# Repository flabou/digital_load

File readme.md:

# Digital load
This is a digital load circuit, project is WIP.
Intended features are:
- USB type-C connector with USB-2.0 supply (5V 500mA)
- Oled display to show current setting (and maybe other stuff)
- Encoder wheel with push-button to change current value
- Ability to connect several circuit (only one with screen, encoder, and usb supply) which will communicate through I2C and share the load (to reach higher current load)
- Several sense resistors to increase dynamic range.
- Maximum current and voltage are to be determined, current will probably be on the order of 1 to 5 amps max, ~1uA min
- USB serial interface, maybe to control from computer and read measured current points, this would allow to specify curve for the load for instance, if there's a use for it.

# Screenshots

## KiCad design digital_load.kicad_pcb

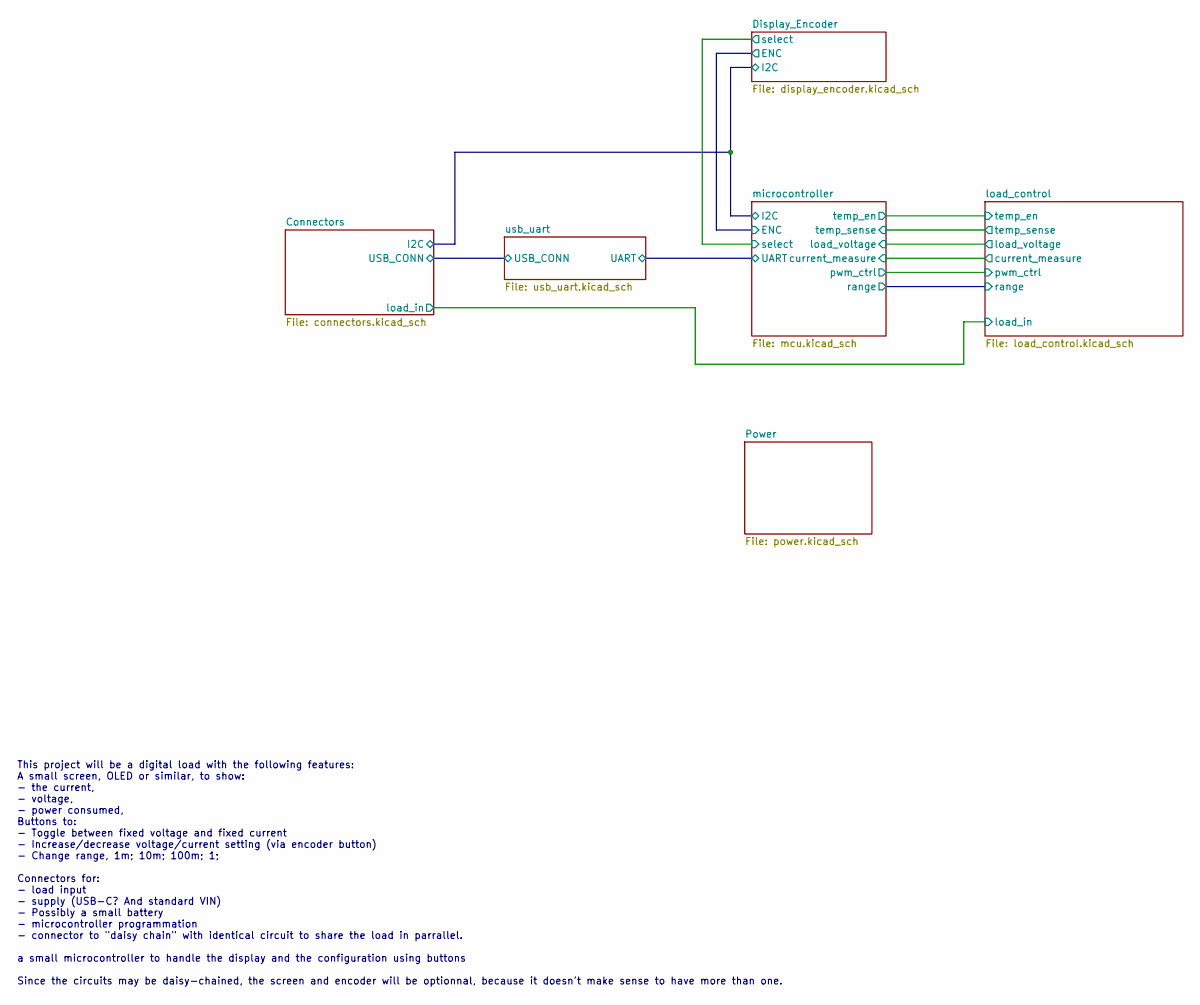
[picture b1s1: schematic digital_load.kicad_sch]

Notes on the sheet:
This project will be a digital load with the following features: A small screen, OLED or similar, to show: - the current, - voltage, - power consumed, Buttons to: - Toggle between fixed voltage and fixed current - Increase/decrease voltage/current setting (via encoder button) - Change range, 1m; 10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

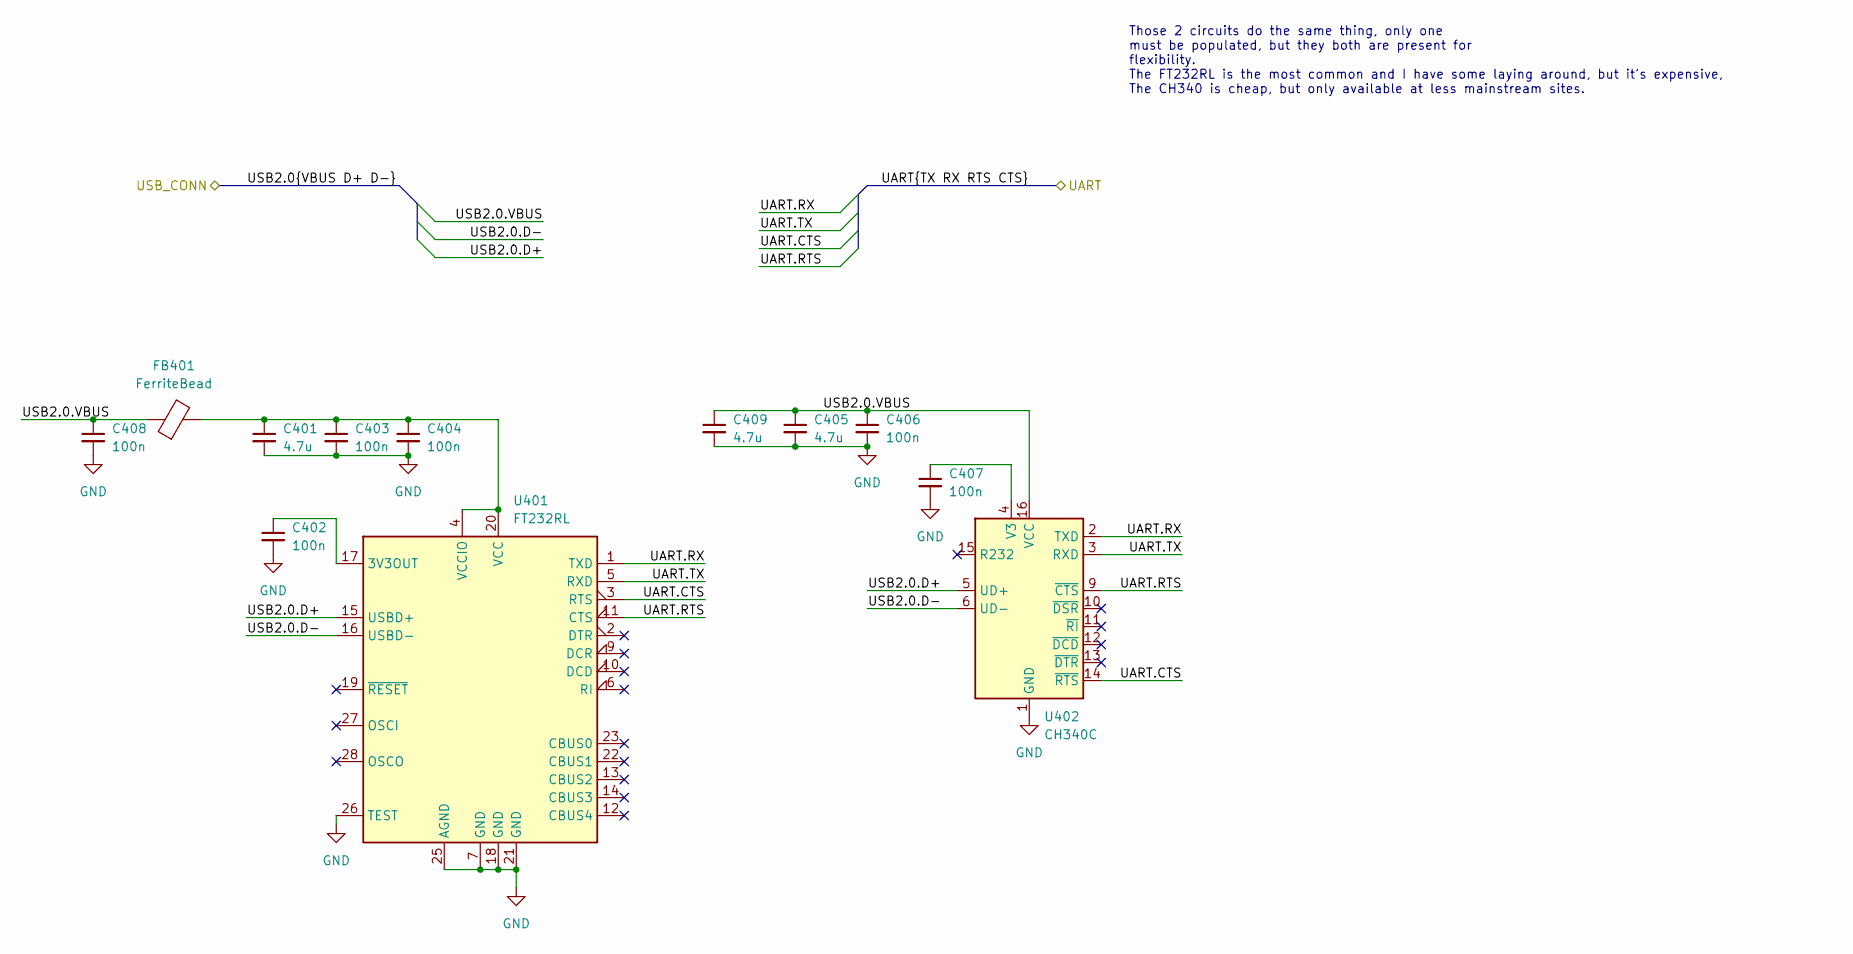
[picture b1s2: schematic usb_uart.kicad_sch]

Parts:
C401, C405, C409: 4.7u; C_0805_2012Metric; PartNumber Generic
C402, C403, C404, C406, C407, C408: 100n; C_0402_1005Metric; PartNumber Generic
FB401: FerriteBead; L_0805_2012Metric; PartNumber MH2029-400Y
U401: FT232RL; SSOP-28_5.3x10.2mm_P0.65mm; PartNumber FT232RL
U402: CH340C; SOIC-16_3.9x9.9mm_P1.27mm; PartNumber CH340C

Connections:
+5V: C405.1, C406.1, C408.1, C409.1, FB401.1, U402.16 (VCC); also elsewhere on the board
/Connectors/USB2.0.D+: U401.15 (USBD+), U402.5 (UD+); also elsewhere on the board
/Connectors/USB2.0.D-: U401.16 (USBD-), U402.6 (UD-); also elsewhere on the board
/microcontroller/UART.CTS: U401.3 (RTS), U402.14 (~RTS); also elsewhere on the board
/microcontroller/UART.RTS: U401.11 (CTS), U402.9 (~CTS); also elsewhere on the board
/microcontroller/UART.RX: U401.1 (TXD), U402.2 (TXD); also elsewhere on the board
/microcontroller/UART.TX: U401.5 (RXD), U402.3 (RXD); also elsewhere on the board
GND: C401.2, C402.2, C403.2, C404.2, C405.2, C406.2, C407.2, C408.2, C409.2, U401.7 (GND), U401.18 (GND), U401.21 (GND), U401.25 (AGND), U401.26 (TEST), U402.1 (GND); also elsewhere on the board
unnamed: C401.1, C403.1, C404.1, FB401.2, U401.4 (VCCIO), U401.20 (VCC)
unnamed: C402.1, U401.17 (3V3OUT)
unnamed: C407.1, U402.4 (V3)

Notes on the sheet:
Those 2 circuits do the same thing, only one must be populated, but they both are present for flexibility. The FT232RL is the most common and I have some laying around, but it's expensive, The CH340 is cheap, but only available at less mainstream sites.

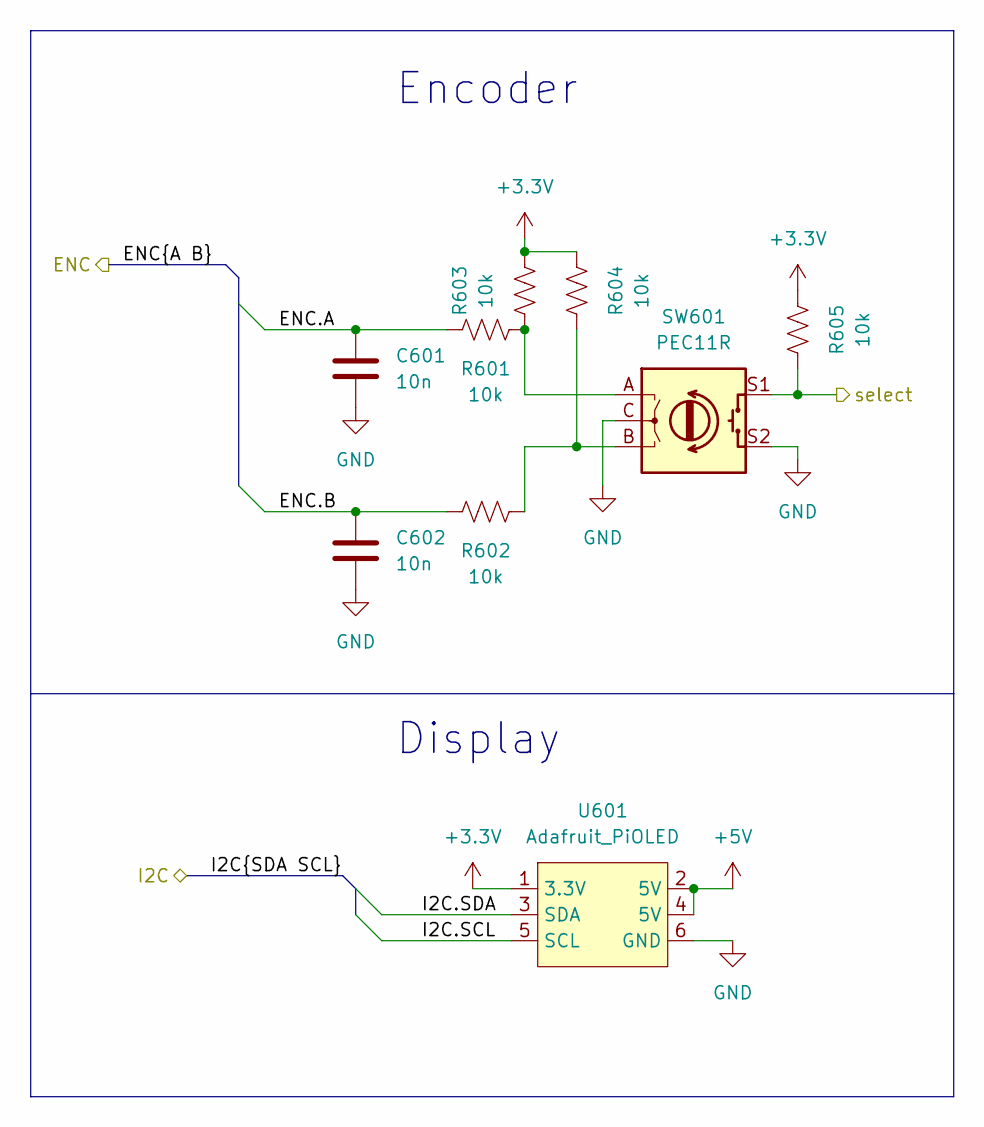
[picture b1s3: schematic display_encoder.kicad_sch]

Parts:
C601, C602: 10n; C_0805_2012Metric; PartNumber Generic
R601, R602, R603, R604, R605: 10k; R_0805_2012Metric; PartNumber Generic
SW601: PEC11R; RotaryEncoder_Alps_EC12E-Switch_Vertical_H20mm; PartNumber PEC11R-4215F-S0024
U601: Adafruit_PiOLED; PiOLED; PartNumber PiOled

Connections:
+3V3: R603.1, R604.2, R605.2, U601.1 (3.3V); also elsewhere on the board
+5V: U601.2 (5V), U601.4 (5V); also elsewhere on the board
/Connectors/I2C.SCL: U601.5 (SCL); also elsewhere on the board
/Connectors/I2C.SDA: U601.3 (SDA); also elsewhere on the board
/Display_Encoder/ENC.A: C601.2, R601.1; also elsewhere on the board
/Display_Encoder/ENC.B: C602.2, R602.1; also elsewhere on the board
/Display_Encoder/select: R605.1, SW601.S1; also elsewhere on the board
GND: C601.1, C602.1, SW601.C, SW601.S2, U601.6 (GND); also elsewhere on the board
unnamed: R601.2, R603.2, SW601.A
unnamed: R602.2, R604.1, SW601.B

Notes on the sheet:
Encoder
Display

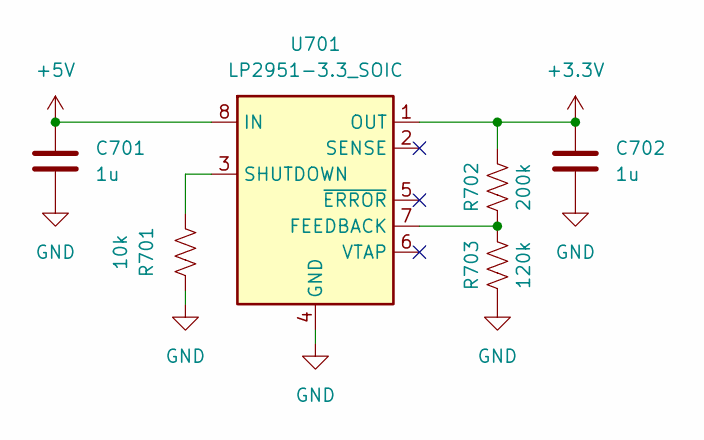
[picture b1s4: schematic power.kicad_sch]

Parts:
C701, C702: 1u; C_0805_2012Metric; PartNumber Generic
R701: 10k; R_0805_2012Metric; PartNumber Generic
R702: 200k; R_0805_2012Metric; PartNumber Generic
R703: 120k; R_0805_2012Metric; PartNumber Generic
U701: LP2951-3.3_SOIC; SOIC-8_3.9x4.9mm_P1.27mm; PartNumber LP2951-30D

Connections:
+3V3: C702.1, R702.1, U701.1 (OUT); also elsewhere on the board
+5V: C701.1, U701.8 (IN); also elsewhere on the board
GND: C701.2, C702.2, R701.2, R703.2, U701.4 (GND); also elsewhere on the board
unnamed: R701.1, U701.3 (SHUTDOWN)
unnamed: R702.2, R703.1, U701.7 (FEEDBACK)

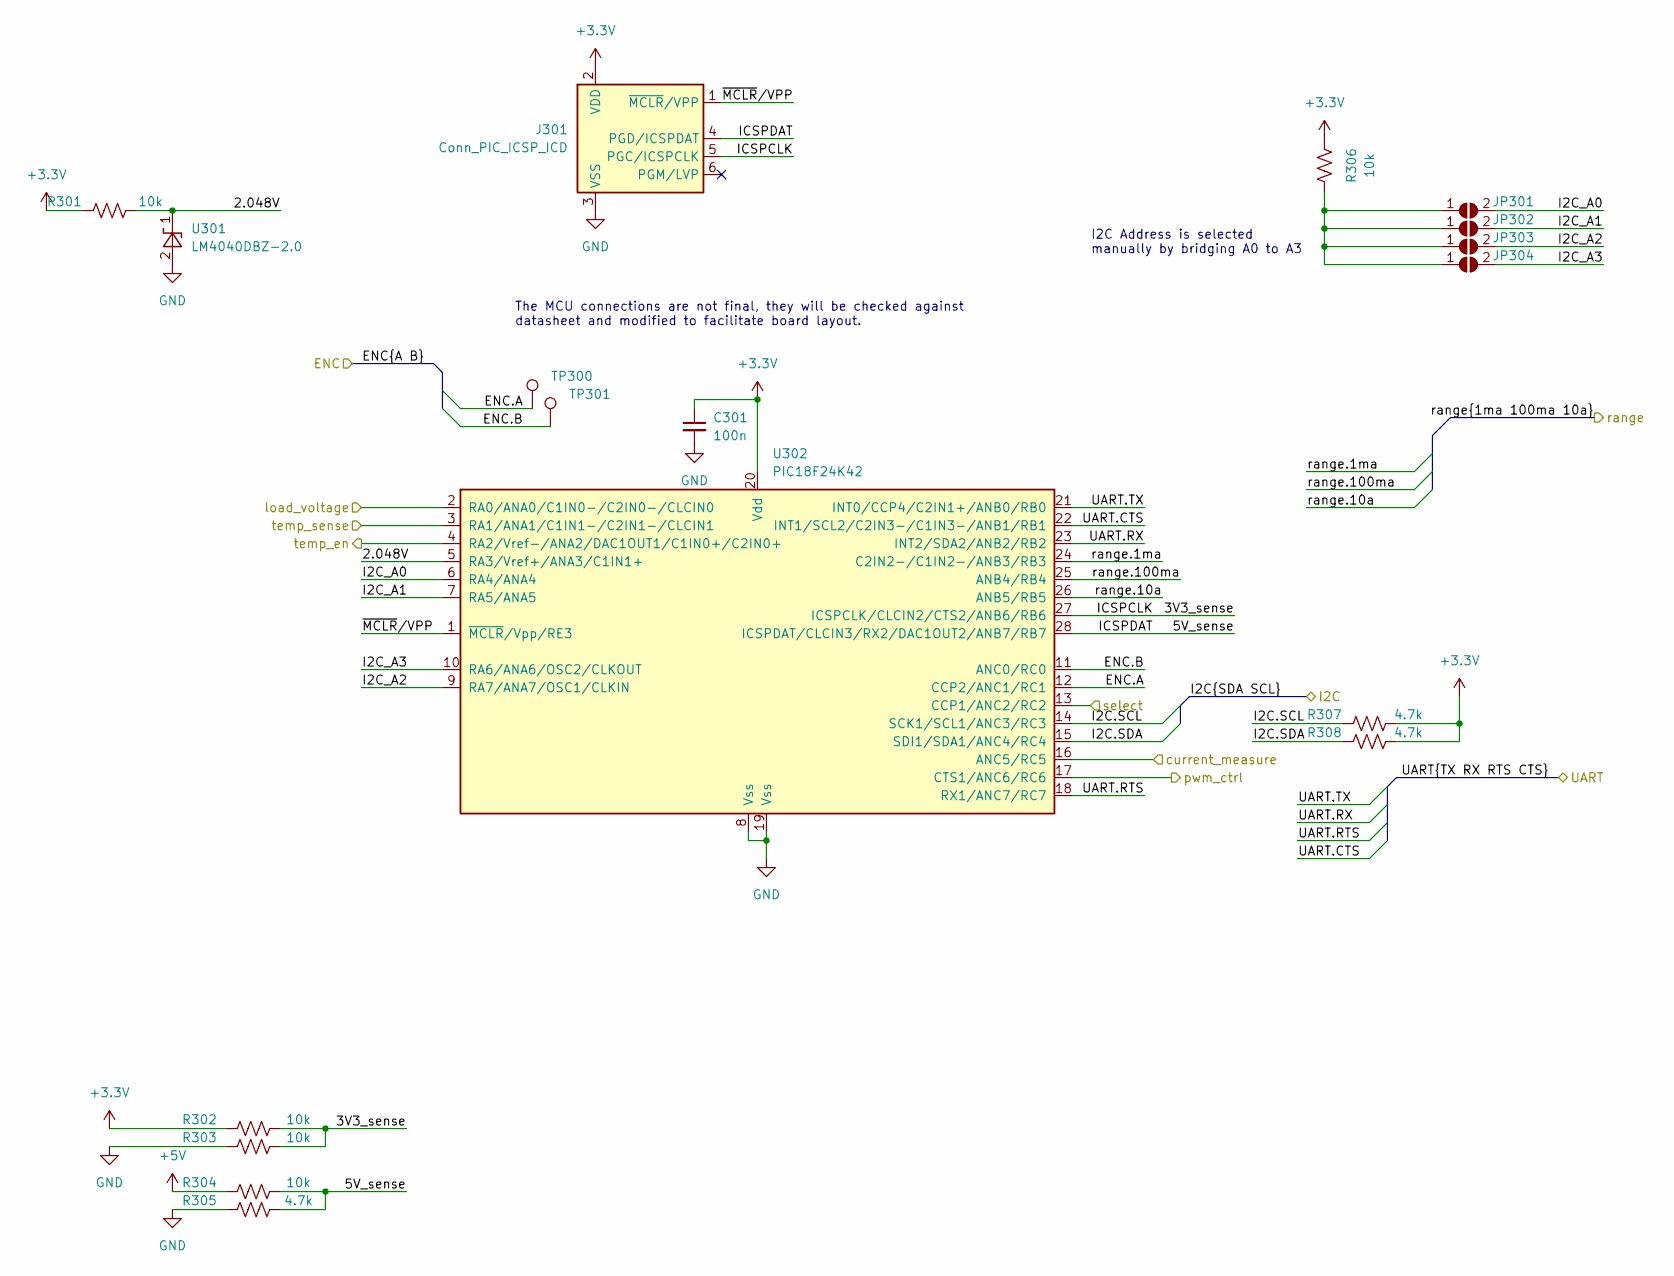
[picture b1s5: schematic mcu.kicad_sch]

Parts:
C301: 100n; C_0402_1005Metric; PartNumber Generic
J301: Conn_PIC_ICSP_ICD; PinHeader_1x06_P2.54mm_Vertical; PartNumber Generic
JP301, JP302, JP303, JP304: SB; SolderJumper-2_P1.3mm_Open_TrianglePad1.0x1.5mm; PartNumber N.A.
R301, R302, R303, R304, R306: 10k; R_0805_2012Metric; PartNumber Generic
R305, R307, R308: 4.7k; R_0805_2012Metric; PartNumber Generic
TP300, TP301: TestPoint_Pad_D1.0mm; PartNumber N.A.
U301: LM4040DBZ-2.0; SOT-23; PartNumber LM4040C20QDBZT
U302: PIC18F24K42; SSOP-28_5.3x10.2mm_P0.65mm; PartNumber PIC18F24K42

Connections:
+3V3: C301.1, J301.2 (VDD), R301.2, R302.2, R306.2, R307.1, R308.1, U302.20 (Vdd); also elsewhere on the board
+5V: R304.2; also elsewhere on the board
/Connectors/I2C.SCL: R307.2, U302.14 (SCK1/SCL1/ANC3/RC3); also elsewhere on the board
/Connectors/I2C.SDA: R308.2, U302.15 (SDI1/SDA1/ANC4/RC4); also elsewhere on the board
/Display_Encoder/ENC.A: TP300.1, U302.12 (CCP2/ANC1/RC1); also elsewhere on the board
/Display_Encoder/ENC.B: TP301.1, U302.11 (ANC0/RC0); also elsewhere on the board
/Display_Encoder/select: U302.13 (CCP1/ANC2/RC2); also elsewhere on the board
/load_control/current_measure: U302.16 (ANC5/RC5); also elsewhere on the board
/load_control/load_voltage: U302.2 (RA0/ANA0/C1IN0-/C2IN0-/CLCIN0); also elsewhere on the board
/load_control/pwm_ctrl: U302.17 (CTS1/ANC6/RC6); also elsewhere on the board
/load_control/range.1ma: U302.24 (C2IN2-/C1IN2-/ANB3/RB3); also elsewhere on the board
/load_control/range.10a: U302.26 (ANB5/RB5); also elsewhere on the board
/load_control/range.100ma: U302.25 (ANB4/RB4); also elsewhere on the board
/load_control/temp_en: U302.4 (RA2/Vref-/ANA2/DAC1OUT1/C1IN0+/C2IN0+); also elsewhere on the board
/load_control/temp_sense: U302.3 (RA1/ANA1/C1IN1-/C2IN1-/CLCIN1); also elsewhere on the board
/microcontroller/2.048V: R301.1, U301.1 (K), U302.5 (RA3/Vref+/ANA3/C1IN1+)
/microcontroller/3V3_sense: J301.5 (PGC/ICSPCLK), R302.1, R303.2, U302.27 (ICSPCLK/CLCIN2/CTS2/ANB6/RB6)
/microcontroller/5V_sense: J301.4 (PGD/ICSPDAT), R304.1, R305.2, U302.28 (ICSPDAT/CLCIN3/RX2/DAC1OUT2/ANB7/RB7)
/microcontroller/I2C_A0: JP301.2 (B), U302.6 (RA4/ANA4)
/microcontroller/I2C_A1: JP302.2 (B), U302.7 (RA5/ANA5)
/microcontroller/I2C_A2: JP303.2 (B), U302.9 (RA7/ANA7/OSC1/CLKIN)
/microcontroller/I2C_A3: JP304.2 (B), U302.10 (RA6/ANA6/OSC2/CLKOUT)
/microcontroller/UART.CTS: U302.22 (INT1/SCL2/C2IN3-/C1IN3-/ANB1/RB1); also elsewhere on the board
/microcontroller/UART.RTS: U302.18 (RX1/ANC7/RC7); also elsewhere on the board
/microcontroller/UART.RX: U302.23 (INT2/SDA2/ANB2/RB2); also elsewhere on the board
/microcontroller/UART.TX: U302.21 (INT0/CCP4/C2IN1+/ANB0/RB0); also elsewhere on the board
/microcontroller/~MCLR/VPP: J301.1 (~MCLR/VPP), U302.1 (~MCLR/Vpp/RE3)
GND: C301.2, J301.3 (VSS), R303.1, R305.1, U301.2 (A), U302.8 (Vss), U302.19 (Vss); also elsewhere on the board
unnamed: JP301.1 (A), JP302.1 (A), JP303.1 (A), JP304.1 (A), R306.1

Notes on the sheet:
I2C Address is selected manually by bridging A0 to A3
The MCU connections are not final, they will be checked against datasheet and modified to facilitate board layout.

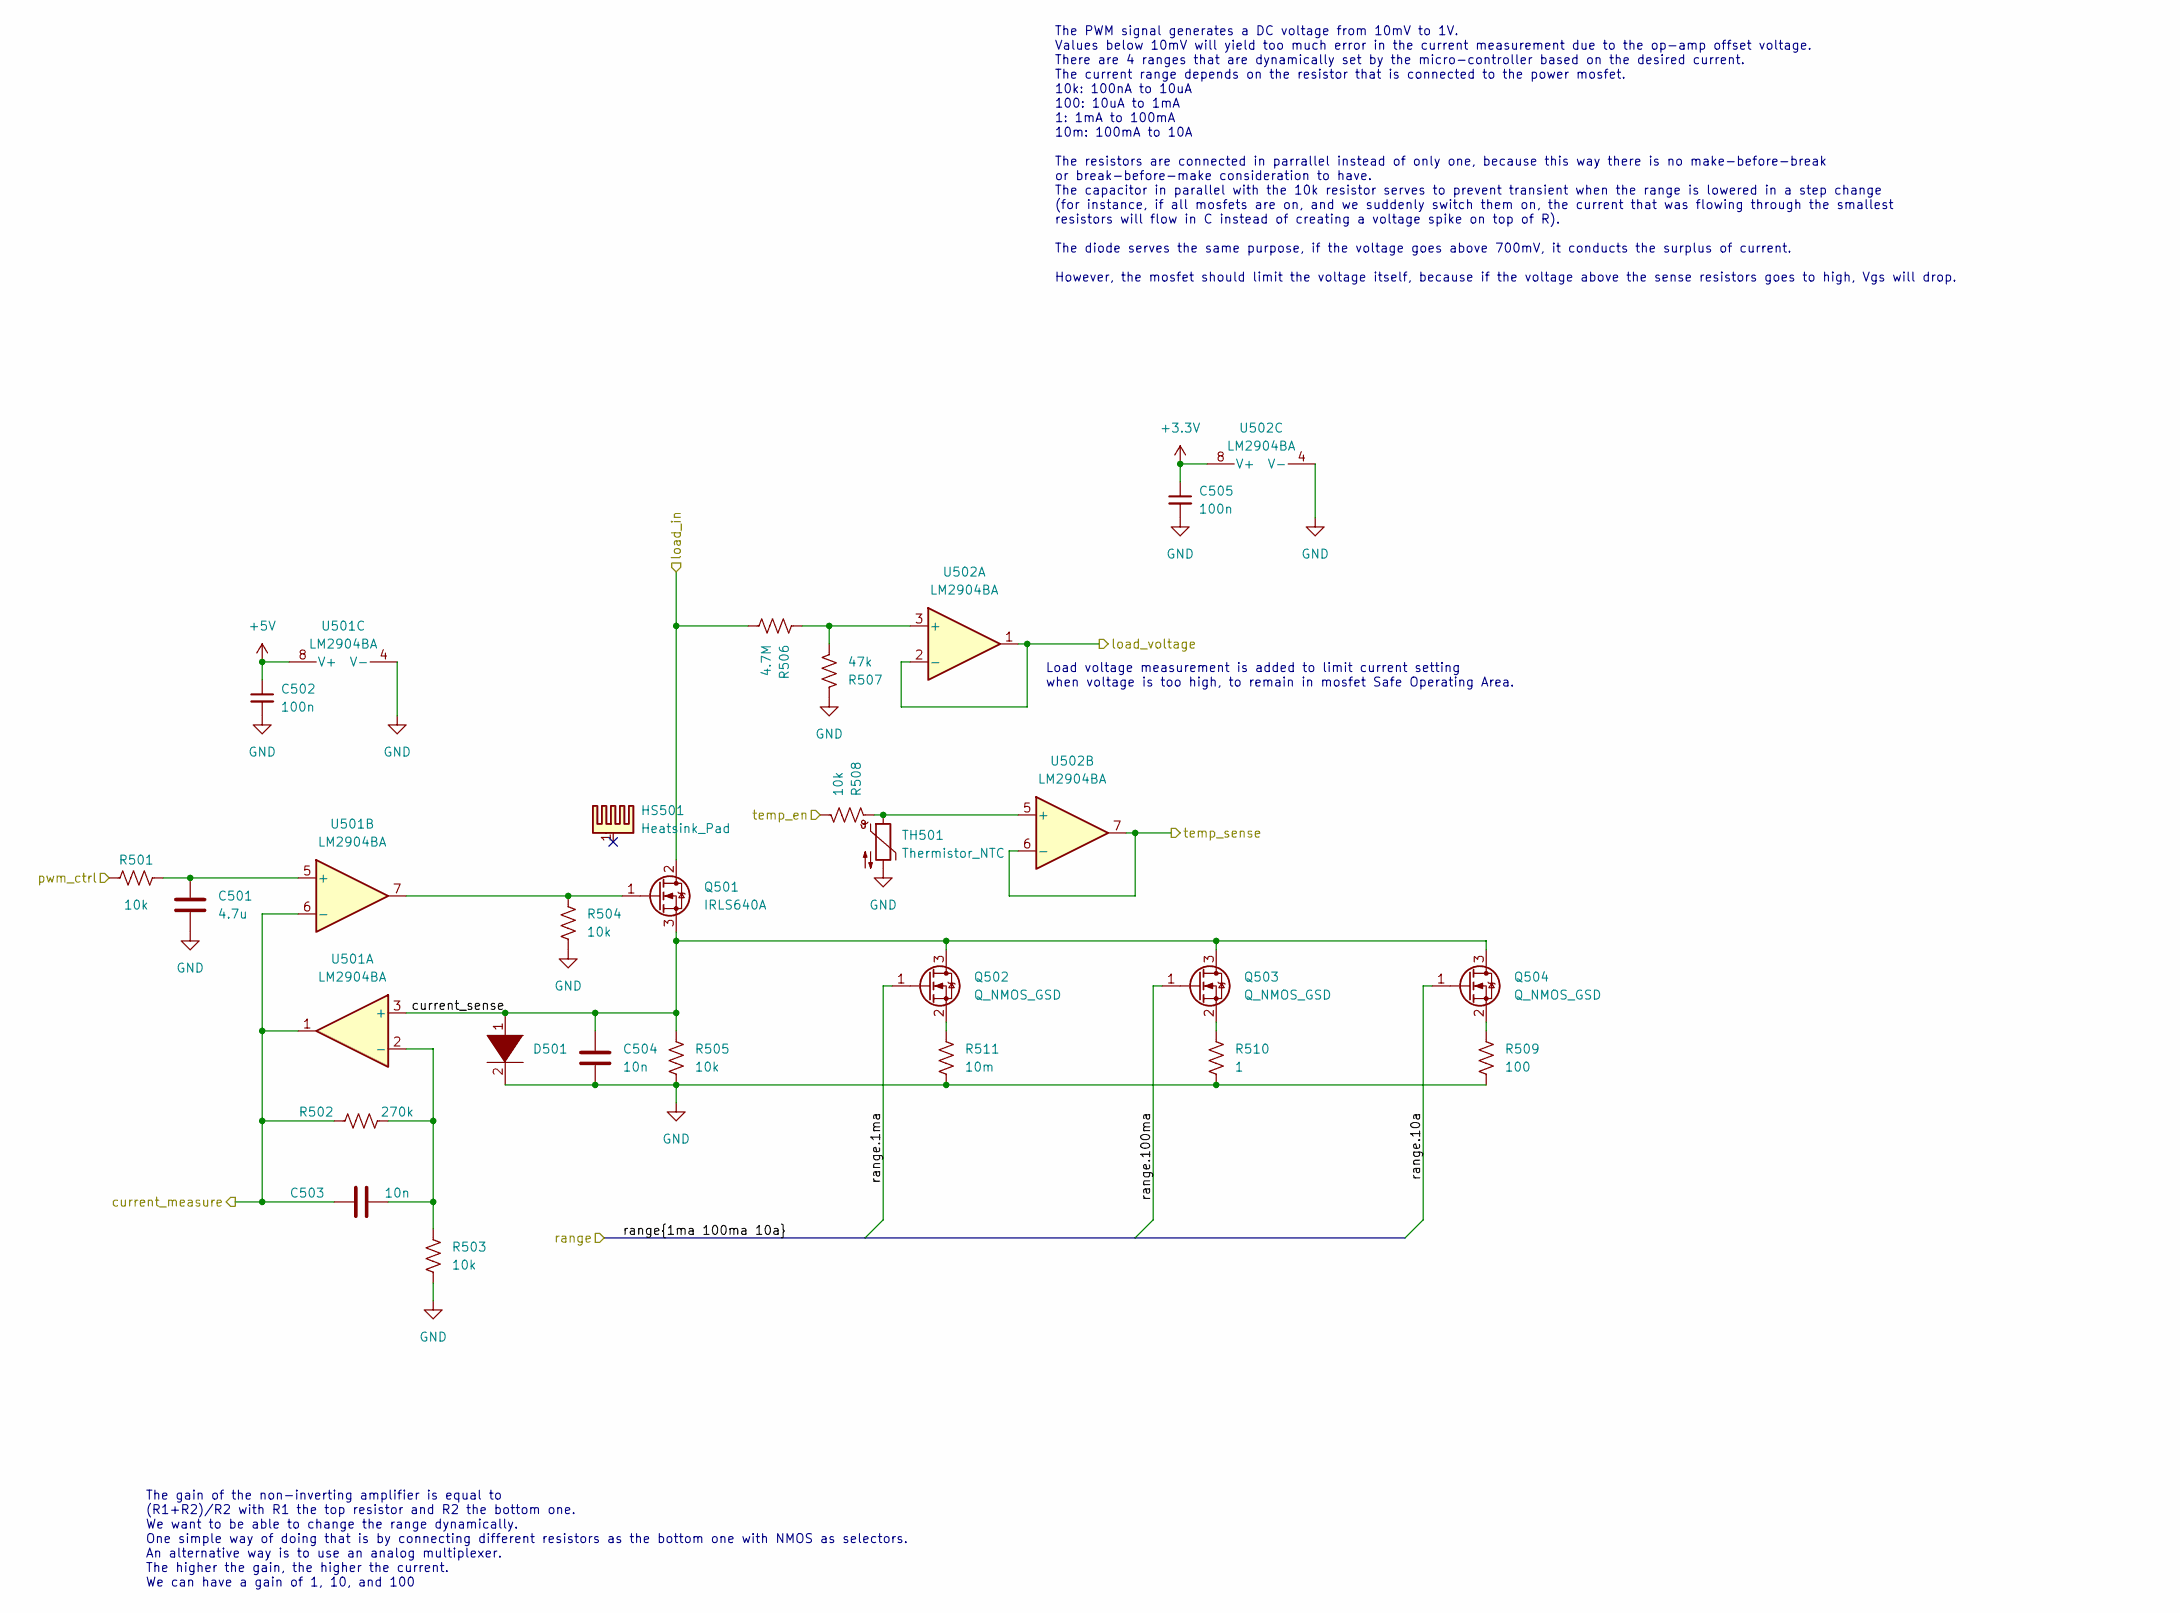
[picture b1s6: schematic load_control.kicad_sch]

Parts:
C501: 4.7u; C_0805_2012Metric; PartNumber Generic
C502, C505: 100n; C_0402_1005Metric; PartNumber Generic
C503, C504: 10n; C_0805_2012Metric; PartNumber Generic
D501: DIODE; D_SOD-323; PartNumber SD101AWS-TP
HS501: Heatsink_Pad; Heatsink_ASSMANN_WSW_V6560W; PartNumber V6560W
Q501: IRLS640A; TO-220-3_Vertical; PartNumber IRLS640A
Q502, Q503, Q504: Q_NMOS_GSD; SOT-23; PartNumber PJA3404_R1_00001
R501, R503, R504, R505, R508: 10k; R_0805_2012Metric; PartNumber Generic
R502: 270k; R_0805_2012Metric; PartNumber Generic
R506: 4.7M; R_0805_2012Metric; PartNumber Generic
R507: 47k; R_0805_2012Metric; PartNumber Generic
R509: 100; R_0805_2012Metric; PartNumber Generic
R510: 1; R_0805_2012Metric; PartNumber Generic
R511: 10m; R_0805_2012Metric; PartNumber Generic
TH501: Thermistor_NTC; R_0402_1005Metric; PartNumber NTCG103JF103FT1
U501, U502: LM2904BA; TSSOP-8_4.4x3mm_P0.65mm; PartNumber LM2904BAIPWR

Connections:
+3V3: C505.1, U502.8 (V+); also elsewhere on the board
+5V: C502.1, U501.8 (V+); also elsewhere on the board
/Connectors/load_in: Q501.2 (D), R506.1; also elsewhere on the board
/load_control/current_measure: C503.2, R502.2, U501.1, U501.6 (-); also elsewhere on the board
/load_control/current_sense: C504.2, D501.1 (K), Q501.3 (S), Q502.3 (D), Q503.3 (D), Q504.3 (D), R505.2, U501.3 (+)
/load_control/load_voltage: U502.1, U502.2 (-); also elsewhere on the board
/load_control/pwm_ctrl: R501.1; also elsewhere on the board
/load_control/range.1ma: Q502.1 (G); also elsewhere on the board
/load_control/range.10a: Q504.1 (G); also elsewhere on the board
/load_control/range.100ma: Q503.1 (G); also elsewhere on the board
/load_control/temp_en: R508.1; also elsewhere on the board
/load_control/temp_sense: U502.6 (-), U502.7; also elsewhere on the board
GND: C501.2, C502.2, C504.1, C505.2, D501.2 (A), R503.2, R504.1, R505.1, R507.2, R509.1, R510.1, R511.1, TH501.2, U501.4 (V-), U502.4 (V-); also elsewhere on the board
unnamed: C501.1, R501.2, U501.5 (+)
unnamed: C503.1, R502.1, R503.1, U501.2 (-)
unnamed: Q501.1 (G), R504.2, U501.7
unnamed: Q502.2 (S), R511.2
unnamed: Q503.2 (S), R510.2
unnamed: Q504.2 (S), R509.2
unnamed: R506.2, R507.1, U502.3 (+)
unnamed: R508.2, TH501.1, U502.5 (+)

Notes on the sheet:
Load voltage measurement is added to limit current setting when voltage is too high, to remain in mosfet Safe Operating Area.
The gain of the non-inverting amplifier is equal to (R1+R2)/R2 with R1 the top resistor and R2 the bottom one. We want to be able to change the range dynamically. One simple way of doing that is by connecting different resistors as the bottom one with NMOS as selectors. An alternative way is to use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
The PWM signal generates a DC voltage from 10mV to 1V. Values below 10mV will yield too much error in the current measurement due to the op-amp offset voltage. There are 4 ranges that are dynamically set by the micro-controller based on the desired current. The current range depends on the resistor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

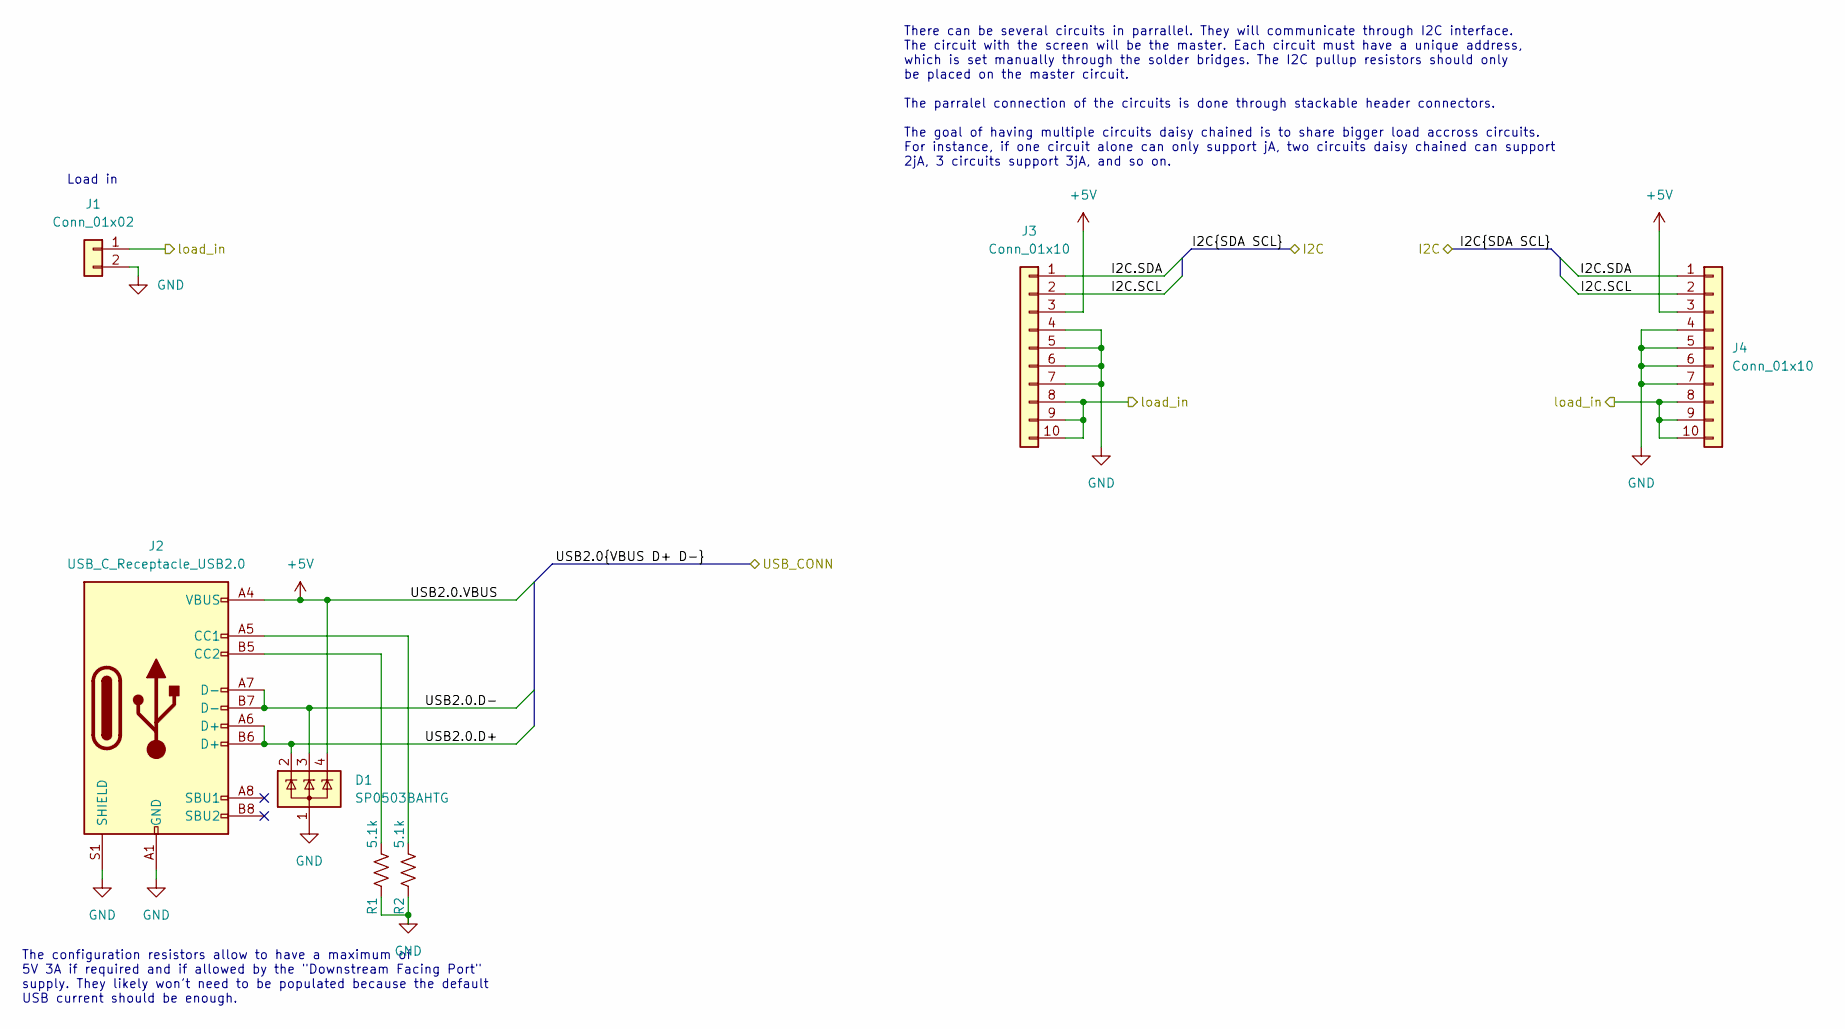
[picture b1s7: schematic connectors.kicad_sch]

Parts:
D1: SP0503BAHTG; SOT-143; PartNumber SP0503BAHTG
J1: Conn_01x02; PinHeader_1x02_P2.54mm_Horizontal; PartNumber Generic
J2: USB_C_Receptacle_USB2.0; USB_C_Receptacle_GCT_USB4085; PartNumber USB4085
J3, J4: Conn_01x10; PinSocket_1x10_P2.54mm_Vertical; PartNumber Generic
R1, R2: 5.1k; R_0805_2012Metric; PartNumber Generic

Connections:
+5V: D1.4 (K), J2.A4 (VBUS), J2.A9 (VBUS), J2.B4 (VBUS), J2.B9 (VBUS), J3.3, J4.3; also elsewhere on the board
/Connectors/I2C.SCL: J3.2, J4.2; also elsewhere on the board
/Connectors/I2C.SDA: J3.1, J4.1; also elsewhere on the board
/Connectors/USB2.0.D+: D1.2 (K), J2.A6 (D+), J2.B6 (D+); also elsewhere on the board
/Connectors/USB2.0.D-: D1.3 (K), J2.A7 (D-), J2.B7 (D-); also elsewhere on the board
/Connectors/load_in: J1.1, J3.8, J3.9, J3.10, J4.8, J4.9, J4.10; also elsewhere on the board
GND: D1.1 (A), J1.2, J2.A1 (GND), J2.A12 (GND), J2.B1 (GND), J2.B12 (GND), J2.S1 (SHIELD), J3.4, J3.5, J3.6, J3.7, J4.4, J4.5, J4.6, J4.7, R1.1, R2.1; also elsewhere on the board
unnamed: J2.A5 (CC1), R2.2
unnamed: J2.B5 (CC2), R1.2

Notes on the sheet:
The configuration resistors allow to have a maximum of 5V 3A if required and if allowed by the "Downstream Facing Port" supply. They likely won't need to be populated because the default USB current should be enough.
There can be several circuits in parrallel. They will communicate through I2C interface. The circuit with the screen will be the master. Each circuit must have a unique address, which is set manually through the solder bridges. The I2C pullup resistors should only be placed on the master circuit. T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
Load in

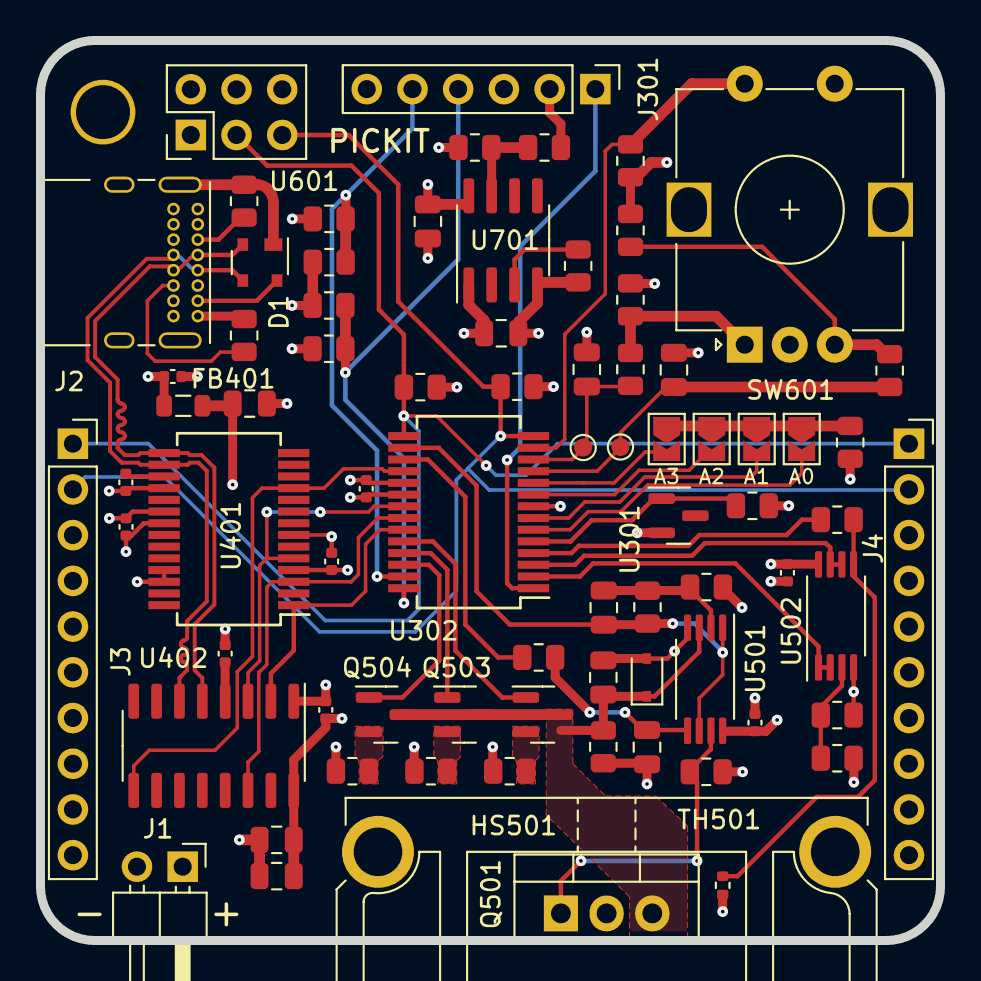
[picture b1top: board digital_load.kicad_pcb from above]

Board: 4 copper layers, 50.0 x 50.0 mm, 77 parts (0 on the bottom side), 50 nets.

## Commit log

2022-04-09 Replace UART{R,L} with I2C
2022-04-09 Add voltage reference and voltage regulator
2022-04-11 Add uart usb controller
2022-04-12 Fix lots of small things
2022-04-12 Arrange components of subcircuits
2022-04-17 WIP PCB Routing + Add load voltage measure
2022-04-18 WIP PCB Routing
2022-04-18 Add licence and readme.md
2022-04-23 Add heatsink, among other things
2022-04-24 WIP routing
2022-04-26 Routing almost complete
2022-04-29 Fix and tune differential pair and zones
2022-04-30 Add partnumbers
2022-04-30 Add bom generator based on kicad examples
2022-05-01 Fix missing footprints in schematic
2022-05-01 Add feedback resistors for regulator
2022-05-02 Change some partnumbers in preparation for the order
2022-05-02 Unclutter silk screen
2022-05-03 Reduce trace resistance of 10mOhm channel
2022-05-03 Add round-tracks edition of PCB
2022-05-03 Update readme screenshots
2022-05-03 Add interractive bom
2022-05-17 Generate interactive bom for main and peripheral variants
